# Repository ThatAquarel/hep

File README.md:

# [Dawson HEP](https://youtu.be/Yp-H1ZBjPuM)

Introduction Video:

## About us

**The Dawson High Energy Physics** club, run by Dr. Manuel Toharia Zapata is a place for curious college students to learn more about particle physics. Every week, students from a wide variety of programs meet to learn and discuss about flavour physisc, extra dimensions and much more. We engage with both theory and experiments, learning about and observing particles. Our many projects include an Alpha particle detector, spark chamber, Scintillating Chamber, and more.

Here's a [video](https://youtu.be/Yp-H1ZBjPuM) about our group!

### [Alpha particle detector](./alpha_particle/README.md)

A solid-state alpha particle detector based off of [CERN'S DIY Alpha Particle Detector](https://github.com/ozel/DIY_particle_detector) design.

### [Higgs data analysis](./higgs_data_analysis/README.md)

Analyzing data from a Monte Carlo simulation to determine the mass of a hidden particle. This program is capable of finding a deviation from the noise and identify the mass of the unexpected particle.

### [Scintillating Chamber](./scintillator_field/README.md)

Our proposal to the 2025 [Beamline for schools](https://beamlineforschools.cern/) competition. It consists of an arrangement of scitillator rods to detect and model the trajectory of cosmic ray in three dimensions. The possible trajectories are then calculated and displayed graphically to the user.

**See Paper [HERE](./scintillator_field/proposal/proposal.pdf)**

## Contacts

- Milo Belarbi
- David Birnbaum
- Tykhon Byshkin
- Matvey Chirchikov
- Danah Dézémé
- Arij Mohamedi
- [Evan Parasol](https://github.com/TheBookwyrms), blackdragon6493@gmail.com
- [Leandro Perez-Moran](https://github.com/LudioRex), pemle2007@gmail.com
- Ari Polterovich
- [Tian Yi, Xia](https://github.com/ThatAquarel), xtxiatianyi@gmail.com
- [Andy Yu](https://github.com/Anodymous1), andy.yu@dawsoncollege.qc.ca
- [Aljoscha Ziegler](https://github.com/Questionning), ziegleraljoscha@gmail.com

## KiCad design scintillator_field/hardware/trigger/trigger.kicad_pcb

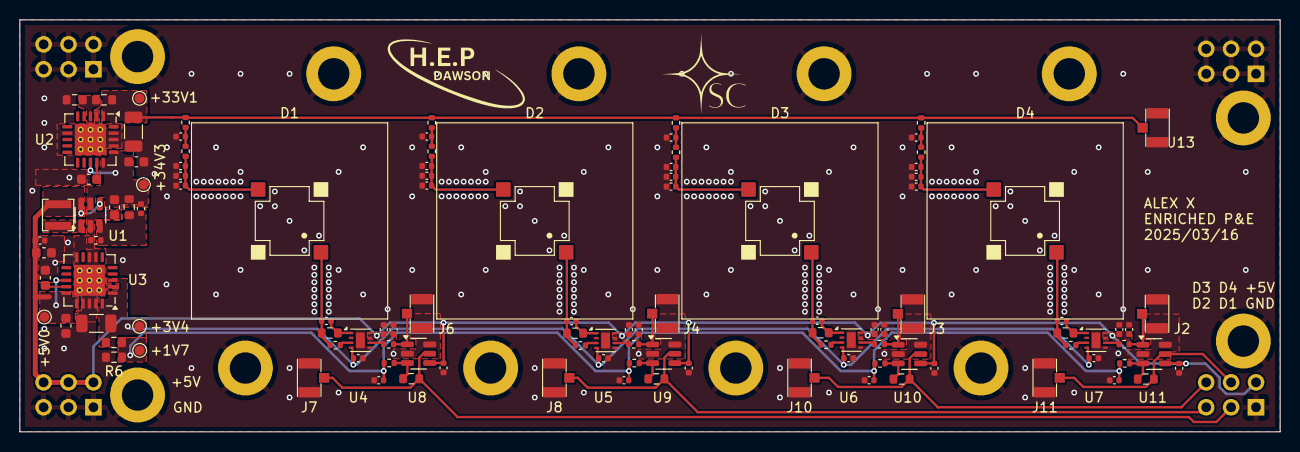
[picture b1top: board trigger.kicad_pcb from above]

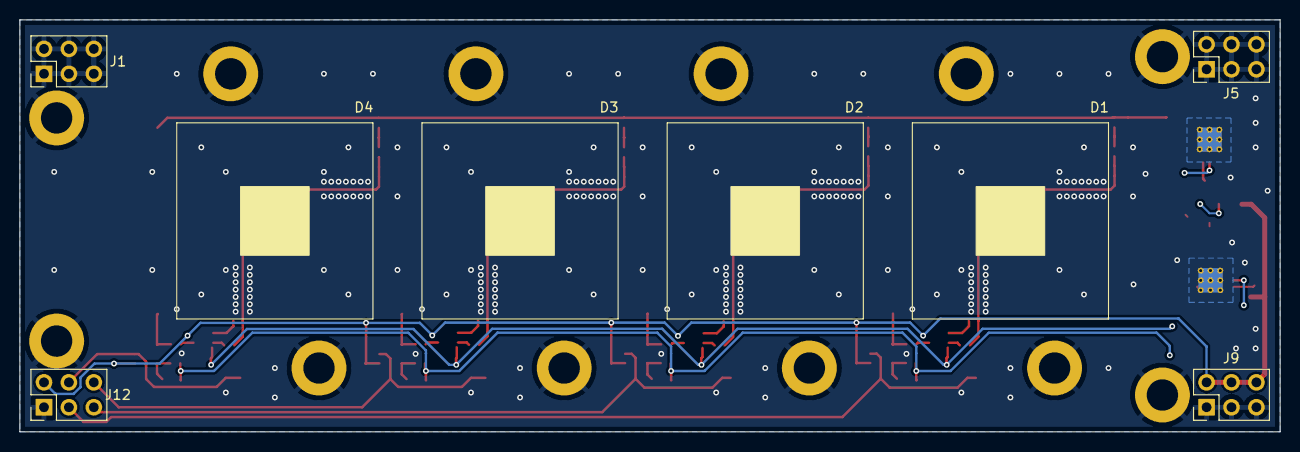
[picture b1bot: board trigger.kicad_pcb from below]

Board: 2 copper layers, 128.5 x 42.0 mm, 130 parts (4 on the bottom side), 47 nets.

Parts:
+1V7, +3V4, +5V0, +33V1, +34V3: TestPoint; TestPoint_Pad_D1.0mm
C1: 22p; C_0402_1005Metric
C2, C31, C32, C33, C34, C41, C42, C43, C44: 0.1u; C_0402_1005Metric
C3, C4, C5, C6, C8, C9: 1u; C_0603_1608Metric
C7, C10: 10u; C_1206_3216Metric
C11, C12, C13, C14, C15, C16, C17, C18, C19, C20, C21, C22, C23, C24, C25, C26, C37, C38, C39, C40, C47, C48, C49, C50: 10n; C_0402_1005Metric
C27, C28, C29, C30: 3p; C_0402_1005Metric
C35, C36, C45, C46: 2.2u; C_0402_1005Metric
D1, D2, D3, D4: MICROFC-60035-SMT-TR SIPM; MICROFC-60035-SMT-TR
H1, H2, H3, H4, H5, H6, H7, H8, H9, H10, H11, H12: M3; MountingHole_3.2mm_M3_DIN965_Pad
J1, J5, J9, J12: Conn_02x03_Top_Bottom; PinHeader_2x03_P2.54mm_Vertical
J2, J3, J4, J6, J7, J8, J10, J11, J13: Conn_Coaxial_Small; BWIPX-1-001E
L1: 22u; L_Murata_LQH3NPN_3.0x3.0mm
R1: 12k 0.1%; R_0402_1005Metric
R2: 316k 0.1%; R_0603_1608Metric
R3, R19, R20, R21, R22: 226k 0.1%; R_0603_1608Metric
R4, R5, R6, R31, R32, R33, R34: 10k 0.1%; R_0603_1608Metric
R7, R8, R9, R10, R11, R12, R13, R14, R27, R28, R29, R30: 49.9R; R_0402_1005Metric
R15, R16, R17, R18: 20R; R_0402_1005Metric
R23, R24, R25, R26: 0; R_0402_1005Metric
U1: LT3461A; TSOT-23-6
U2, U3: TPS7A4701; Texas_RGW0020A_VQFN-20-1EP_5x5mm_P0.65mm_EP3.15x3.15mm_Ther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
U4, U5, U6, U7: OPA858xDSG; WSON-8-1EP_2x2mm_P0.5mm_EP0.9x1.6mm
U8, U9, U10, U11: TLV3501AIDBV; SOT-23-6

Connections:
+1.7V: +1V7.1, C37.1, C38.1, C47.1, C48.1, R5.2, R6.1, R27.2, R28.2, R29.2, R30.2
+3.4V: +3V4.1, C10.1, C39.1, C40.1, C49.1, C50.1, R5.1, U3.1 (OUT), U3.3 (SENSE/FB), U3.20 (OUT), U4.4 (+), U5.4 (+), U6.4 (+), U7.4 (+)
+5V: +5V0.1, C2.1, C3.1, C8.1, C31.1, C32.1, C33.1, C34.1, C35.1, C36.1, C41.1, C42.1, C43.1, C44.1, C45.1, C46.1, J9.4, J9.5, J9.6, J12.4, L1.2, U1.4 (SHDN), U1.6 (VIN), U3.13 (EN), U3.15 (IN), U3.16 (IN), U4.7 (V+), U4.8 (~PD), U5.7 (V+), U5.8 (~PD), U6.7 (V+), U6.8 (~PD), U7.7 (V+), U7.8 (~PD), U8.4 (V+), U9.4 (V+), U10.4 (V+), U11.4 (V+)
+33.1V: +33V1.1, C7.1, J13.1 (In), R3.1, R7.1, R8.1, R9.1, R10.1, U2.1 (OUT), U2.20 (OUT)
+34.3V: +34V3.1, C1.2, C4.1, C5.1, R2.2, U1.5 (VOUT), U2.13 (EN), U2.15 (IN), U2.16 (IN)
/amplifiers/AOUT1: J6.1 (In), R23.2, U8.1 (-)
/amplifiers/AOUT2: J4.1 (In), R24.2, U9.1 (-)
/amplifiers/AOUT3: J3.1 (In), R25.2, U10.1 (-)
/amplifiers/AOUT4: J2.1 (In), R26.2, U11.1 (-)
/amplifiers/DOUT1: J7.1 (In), J12.2, R31.2, U8.5
/amplifiers/DOUT2: J8.1 (In), J12.3, R32.2, U9.5
/amplifiers/DOUT3: J10.1 (In), J12.6, R33.2, U10.5
/amplifiers/DOUT4: J11.1 (In), J12.5, R34.2, U11.5
/amplifiers/IN1: C27.1, D1.2 (A), R15.1, R19.1
/amplifiers/IN2: C28.1, D2.2 (A), R16.1, R20.1
/amplifiers/IN3: C29.1, D3.2 (A), R17.1, R21.1
/amplifiers/IN4: C30.1, D4.2 (A), R18.1, R22.1
GND: C2.2, C3.2, C4.2, C5.2, C6.2, C7.2, C8.2, C9.2, C10.2, C11.2, C12.2, C13.2, C14.2, C15.2, C16.2, C17.2, C18.2, C19.2, C20.2, C21.2, C22.2, C23.2, C24.2, C25.2, C26.2, C31.2, C32.2, C33.2, C34.2, C35.2, C36.2, C37.2, C38.2, C39.2, C40.2, C41.2, C42.2, C43.2, C44.2, C45.2, C46.2, C47.2, C48.2, C49.2, C50.2, H1.1, H2.1, H3.1, H4.1, H5.1, H6.1, H7.1, H8.1, H9.1, H10.1, H11.1, H12.1, J1.1, J1.2, J1.3, J1.4, J1.5, J1.6, J2.2 (Ext), J3.2 (Ext), J4.2 (Ext), J5.1, J5.2, J5.3, J5.4, J5.5, J5.6, J6.2 (Ext), J7.2 (Ext), J8.2 (Ext), J9.1, J9.2, J9.3, J10.2 (Ext), J11.2 (Ext), J12.1, J13.2 (Ext), R1.1, R4.2, R6.2, U1.2 (GND), U2.2 (NC), U2.7 (GND), U2.17 (NC), U2.18 (NC), U2.19 (NC), U2.21 (EP), U3.2 (NC), U3.7 (GND), U3.8 (1.6V), U3.10 (0.4V), U3.17 (NC), U3.18 (NC), U3.19 (NC), U3.21 (EP), U4.5 (V-), U4.9 (V-), U5.5 (V-), U5.9 (V-), U6.5 (V-), U6.9 (V-), U7.5 (V-), U7.9 (V-), U8.2 (V-), U8.6 (SHDN), U9.2 (V-), U9.6 (SHDN), U10.2 (V-), U10.6 (SHDN), U11.2 (V-), U11.6 (SHDN)
unnamed: C11.1, R7.2, R11.1
unnamed: C12.1, R8.2, R12.1
unnamed: C13.1, R9.2, R13.1
unnamed: C14.1, R10.2, R14.1
unnamed: C15.1, C19.1, C23.1, D1.1 (K), R11.2
unnamed: C16.1, C20.1, C24.1, D2.1 (K), R12.2
unnamed: C17.1, C21.1, C25.1, D3.1 (K), R13.2
unnamed: C18.1, C22.1, C26.1, D4.1 (K), R14.2
unnamed: R23.1, U4.6
unnamed: R24.1, U5.6
unnamed: R25.1, U6.6
unnamed: R26.1, U7.6
unnamed: C1.1, R1.2, R2.1, U1.3 (FB)
unnamed: L1.1, U1.1 (SW)
unnamed: C6.1, U2.14 (NR)
unnamed: R3.2, R4.1, U2.3 (SENSE/FB)
unnamed: C9.1, U3.14 (NR)
unnamed: R15.2, U4.3 (-)
unnamed: C27.2, R19.2, U4.1 (FB)
unnamed: R16.2, U5.3 (-)
unnamed: C28.2, R20.2, U5.1 (FB)
unnamed: R17.2, U6.3 (-)
unnamed: C29.2, R21.2, U6.1 (FB)
unnamed: R18.2, U7.3 (-)
unnamed: C30.2, R22.2, U7.1 (FB)
unnamed: R27.1, R31.1, U8.3 (+)
unnamed: R28.1, R32.1, U9.3 (+)
unnamed: R29.1, R33.1, U10.3 (+)
unnamed: R30.1, R34.1, U11.3 (+)

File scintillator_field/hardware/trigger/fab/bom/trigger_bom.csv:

Comment,Designator,Footprint,LCSC
"22p, 50V",C1,Capacitor_SMD:C_0402_1005Metric,C70464
"10n, 50V","C11,C12,C13,C14,C15,C16,C17,C18,C19,C20,C21,C22,C23,C24,C25,C26,C37,C38,C39,C40,C47,C48,C49,C50",Capacitor_SMD:C_0402_1005Metric,C1524
"0.1u, 50V","C2,C31,C32,C33,C34,C41,C42,C43,C44",Capacitor_SMD:C_0402_1005Metric,C1581
"3p, 50V","C27,C28,C29,C30",Capacitor_SMD:C_0402_1005Metric,C1564
"1u, 50V","C3,C4,C5,C6,C8,C9",Capacitor_SMD:C_0603_1608Metric,C15849
"2.2u, 10V","C35,C36,C45,C46",Capacitor_SMD:C_0402_1005Metric,C60078
"10u, 50V","C7,C10",Capacitor_SMD:C_1206_3216Metric,C13585
"Conn_Coaxial_Small, I-PEX MHF1","J2,J3,J4,J6,J7,J8,J10,J11,J13",connectors:BWIPX-1-001E,C496552
22uH,L1,lqh3npn:L_Murata_LQH3NPN_3.0x3.0mm,C237408
12k 0.1%,R1,Resistor_SMD:R_0402_1005Metric,C317927
20R,"R15,R16,R17,R18",Resistor_SMD:R_0402_1005Metric,C25089
316k 0.1%,R2,Resistor_SMD:R_0603_1608Metric,C861317
0R,"R23,R24,R25,R26",Resistor_SMD:R_0402_1005Metric,C17168
226k 0.1%,"R3,R19,R20,R21,R22",Resistor_SMD:R_0603_1608Metric,C861233
10k 0.1%,"R4,R5,R6,R31,R32,R33,R34",Resistor_SMD:R_0603_1608Metric,C136139
49.9R,"R7,R8,R9,R10,R11,R12,R13,R14,R27,R28,R29,R30",Resistor_SMD:R_0402_1005Metric,C25120
LT3461A,U1,Package_TO_SOT_SMD:TSOT-23-6,C481768
TPS7A4701,"U2,U3",Package_DFN_QFN:Texas_RGW0020A_VQFN-20-1EP_5x5mm_P0.65mm_EP3.15x3.15mm_ThermalVias,C90084
OPA858xDSG,"U4,U5,U6,U7",Package_SON:WSON-8-1EP_2x2mm_P0.5mm_EP0.9x1.6mm,C970232
TLV3501AIDBV,"U8,U9,U10,U11",Package_TO_SOT_SMD:SOT-23-6,C193413

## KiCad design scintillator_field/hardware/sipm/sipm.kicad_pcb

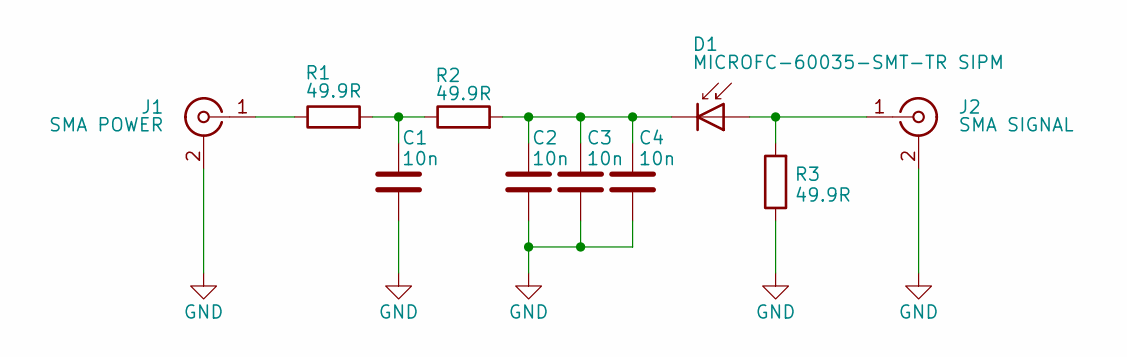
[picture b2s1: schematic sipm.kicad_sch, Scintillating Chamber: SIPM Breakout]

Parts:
C1, C2, C3, C4: 10n; C_0805_2012Metric_Pad1.18x1.45mm_HandSolder
D1: MICROFC-60035-SMT-TR SIPM; MICROFC-60035-SMT-TR
J1: SMA POWER; SMA_Amphenol_901-144_Vertical
J2: SMA SIGNAL; SMA_Amphenol_901-144_Vertical
R1, R2, R3: 49.9R; R_0805_2012Metric_Pad1.20x1.40mm_HandSolder

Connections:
GND: C1.2, C2.2, C3.2, C4.2, J1.2 (Ext), J2.2 (Ext), R3.1
unnamed: C1.1, R1.2, R2.1
unnamed: D1.2 (A), J2.1 (In), R3.2
unnamed: C2.1, C3.1, C4.1, D1.1 (K), R2.2
unnamed: J1.1 (In), R1.1

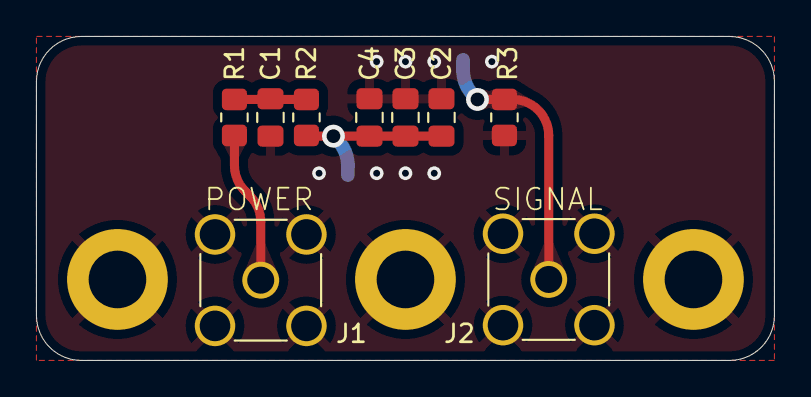
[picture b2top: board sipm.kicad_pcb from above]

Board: 2 copper layers, 41.0 x 18.0 mm, 10 parts (1 on the bottom side), 5 nets.

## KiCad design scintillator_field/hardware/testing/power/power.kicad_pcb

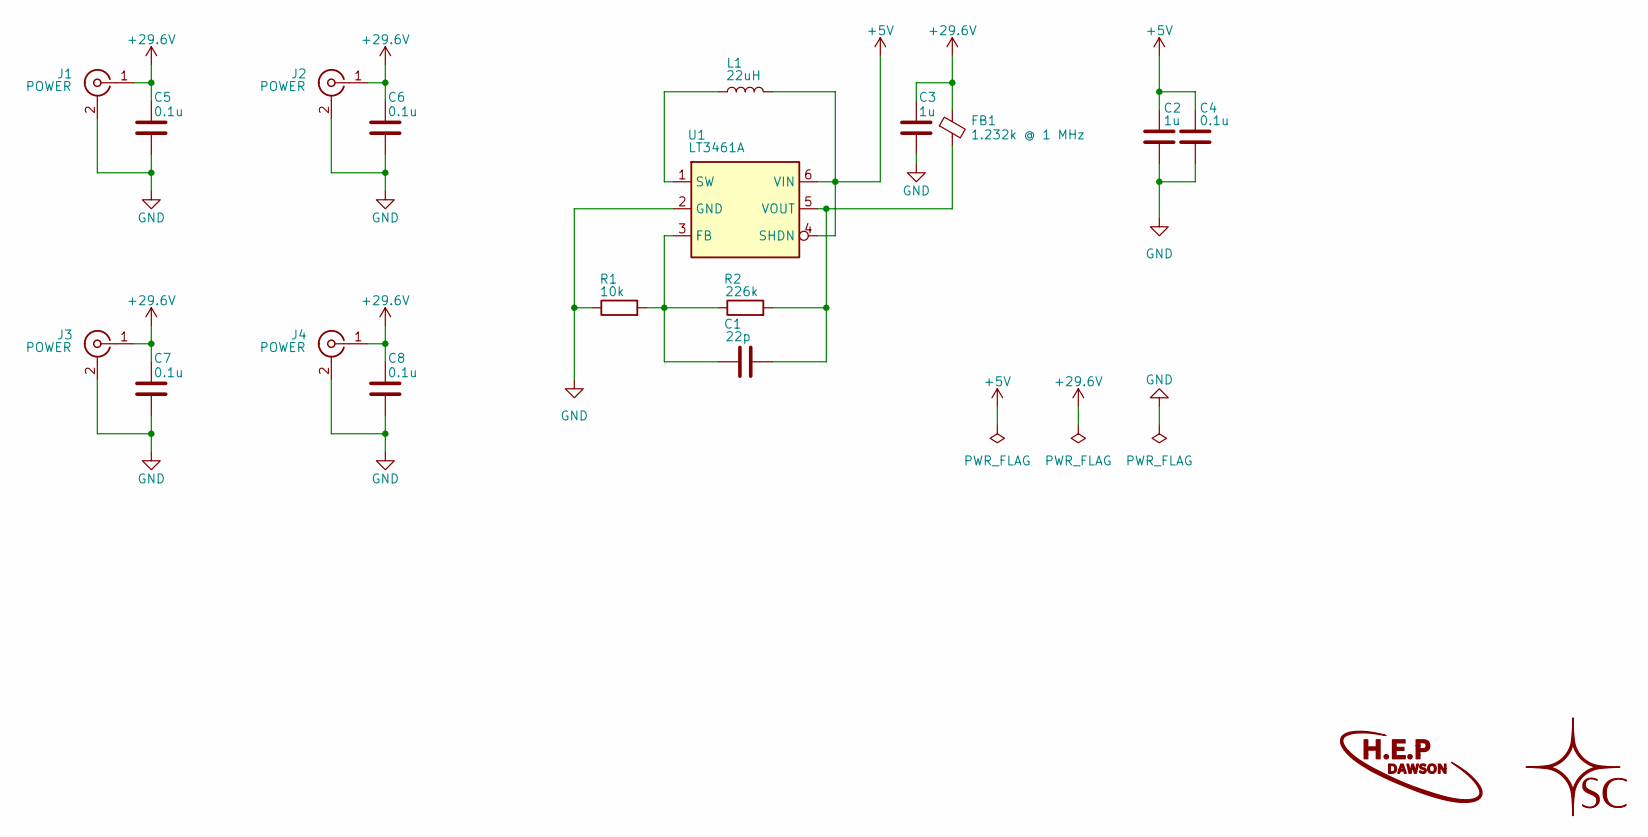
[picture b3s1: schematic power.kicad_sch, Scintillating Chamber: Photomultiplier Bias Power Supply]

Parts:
C1: 22p; C_0805_2012Metric_Pad1.18x1.45mm_HandSolder
C2, C3: 1u; C_0805_2012Metric_Pad1.18x1.45mm_HandSolder
C4, C5, C6, C7, C8: 0.1u; C_0805_2012Metric_Pad1.18x1.45mm_HandSolder
FB1: 1.232k @ 1 MHz; FB_TDK_VFS6045_2424_6060Metric_HandSoldering
J1, J2, J3, J4: POWER; SMA_Amphenol_901-144_Vertical
L1: 22uH; L_Laird_TYS3015_HandSoldering
R1: 10k; R_0805_2012Metric_Pad1.20x1.40mm_HandSolder
R2: 226k; R_0805_2012Metric_Pad1.20x1.40mm_HandSolder
U1: LT3461A; TSOT-23-6_HandSoldering

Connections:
+5V: C2.1, C4.1, L1.2, U1.4 (SHDN), U1.6 (VIN)
+29.6V: C3.1, C5.1, C6.1, C7.1, C8.1, FB1.1, J1.1 (In), J2.1 (In), J3.1 (In), J4.1 (In)
GND: C2.2, C3.2, C4.2, C5.2, C6.2, C7.2, C8.2, J1.2 (Ext), J2.2 (Ext), J3.2 (Ext), J4.2 (Ext), R1.1, U1.2 (GND)
unnamed: C1.1, R1.2, R2.1, U1.3 (FB)
unnamed: L1.1, U1.1 (SW)
unnamed: C1.2, FB1.2, R2.2, U1.5 (VOUT)

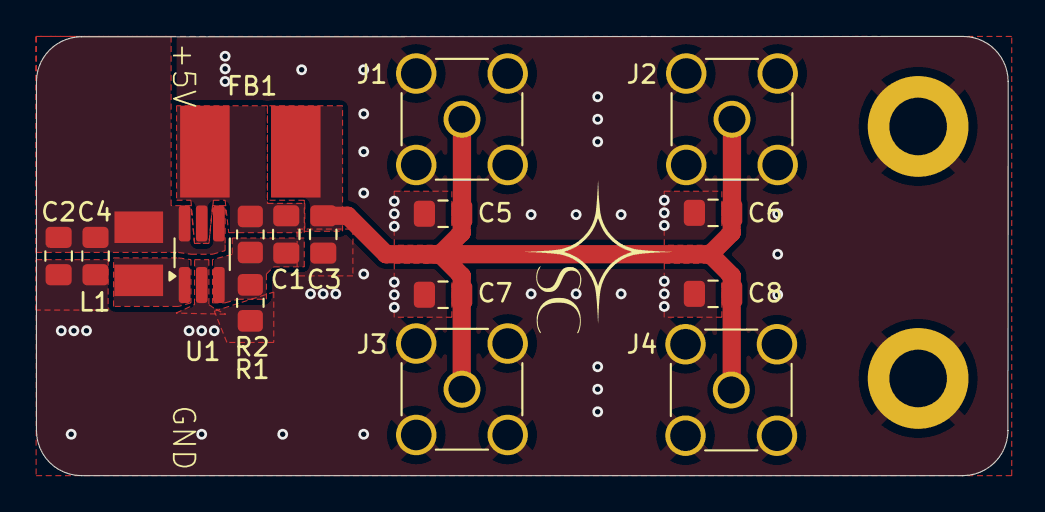
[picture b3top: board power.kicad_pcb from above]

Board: 2 copper layers, 54.0 x 24.4 mm, 17 parts (0 on the bottom side), 6 nets.

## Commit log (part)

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2025-03-17 3D structure rods configuration, x and y axes
2025-03-17 finalize pcb
2025-03-18 clean up display code, add some documentation
2025-03-18 pcb fabrication files
2025-03-18 shaders tests
2025-03-18 shaders mac
2025-03-19 acquisition pcb
2025-03-20 fix trigger pcb
2025-03-20 update to opa858
2025-03-20 fabrication for trigger
2025-03-20 First version of boundary creation algorithm
2025-03-23 usb-c
2025-03-23 fpga pll latching detection
2025-03-24 Implemented input for both side views
2025-03-24 Implemented input for 2 side views
2025-03-26 expensese
2025-03-26 invoice
2025-03-26 receipts
2025-03-26 Create bl4s_proposal.tex
    LaTeX file containing the Scintilating Chamber BL4S proposal. Updated regularly from Proposal.doc on the Google Drive repository: https://drive.google.com/drive/folders/19_MMcoH1Qw7MvBGZwiW7HJuY0r8M6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
2025-03-27 top and bottom sections of detector
2025-03-27 finances
2025-03-27 Added another visualizer(work in progress)
2025-03-28 Now returns hull bounds (y is assumed to be extended)
2025-03-28 visualizer in display_2, if this works
2025-03-28 Famework and rename bl4s_proposal.tex to main.tex
    Added some of the framework for the main file.
2025-03-28 Create README.md (bare bones)
2025-03-28 display_1 uses shaders
2025-03-28 removed opengl matrix viewing and projection functions
2025-03-28 Version that will have bugs
2025-03-28 Removed bugs
2025-03-28 Minor clean up
2025-03-28 show convex hull for arbitraty test points
2025-03-28 integrated Aljoscha's code
2025-03-29 Added code for fans
2025-03-29 Input all section files
2025-03-30 Added binary-to-list function
2025-04-04 Fixed bugs caused by (1, 1) type inputs
2025-04-04 added description.txt
2025-04-05 converted scintillator field to module scintillator_field. hull detection display with points works properly (test data in get_hull_returns), hull detection using detection.py has errors.
2025-04-06 Update acknowledgements.tex
    Full version of the acknowledgements
2025-04-06 Update introduction.tex
    Full version of the introduction. NOT FINAL, subject to change.
2025-04-06 Create community_outreach
2025-04-06 almost ready to go(only have to fix coordinates)
2025-04-06 Fixed the rods lighting up on click feature
2025-04-06 pins of registers
2025-04-06 arduino code
2025-04-06 fpga signal shift register
2025-04-06 serial communication
2025-04-06 new pins
2025-04-07 Test fix
2025-04-07 Fixed reference system
2025-04-07 Cleaner version
2025-04-07 Right values now
2025-04-07 to save
2025-04-08 fixed units
2025-04-08 Converted to class, thanks to Evan!
2025-04-08 Fixed value resetting
2025-04-08 display_1 shows proper display, uses correct size
2025-04-08 fpga all working
2025-04-08 cleanup repo tree
2025-04-08 now works
2025-04-08 serial reading
2025-04-08 arduino input for display_1
2025-04-08 hull_bounds error
2025-04-08 crash error fix attempt
2025-04-09 display and detector work, error patched
2025-04-09 xyz axis
2025-04-09 Changed test.py into a class(data_manager)
2025-04-09 clicking detection now works
2025-04-09 fixed lighting up and added (1,1) compatibility
2025-04-09 works
2025-04-09 fixed typo
2025-04-09 serial testing
2025-04-09 lights up by default
2025-04-09 work
2025-04-09 signal to noise ratio adjustement
2025-04-09 data input & camera clipping
2025-04-09 refactor verilog
2025-04-09 displays time, generate csv
2025-04-10 fixed turning off lighting(also just to save)
2025-04-10 refactor hardware
2025-04-10 refactor acquisition
2025-04-10 display_1 works for real data. data from 2025-04-09 run.
2025-04-10 Fixed lighting up; test.data now has 1 less layer
2025-04-10 latex gitignores
2025-04-10 latex proposal
2025-04-10 Applied binary conversion
2025-04-12 dual display test
2025-04-12 basic refactor for dual viewport
2025-04-12 remove old boundary package
2025-04-12 refactor module
2025-04-12 add convex tests
2025-04-12 testing gitignore
2025-04-12 cleanup tree
2025-04-12 copy impl_b
2025-04-12 basic viewporting impl_a
2025-04-12 dual viewports for impl_a
2025-04-12 add data manager tests
2025-04-12 refactor imports
2025-04-12 dual viewport wrappers
2025-04-12 viewports focus manipulation
2025-04-12 remove impl_b manual entrypoint
2025-04-12 callback none protection
2025-04-12 viewport rendering ratios
2025-04-12 fixed side controls
2025-04-12 load fonts
2025-04-12 add logo + text
2025-04-12 dual viewports testing
2025-04-14 long-term data acquisition
2025-04-16 fix time and location of csv saving windows
2025-04-16 impl a and b data manager and arduino in single file, compatible for both
2025-04-16 data recorder failure add
2025-04-16 long term
2025-04-16 long term print
2025-04-16 set logging level
2025-04-16 first round data
2025-04-17 excel .gitignore
2025-04-17 transfer receipts
2025-04-17 removed fan_out from Evan and Andy's code, still remains in Aljoscha's code. only generates data csv if not debugging (having actual data)
2025-04-17 small refactoring, including minor compatibility fixes
2025-04-17 new data
2025-04-17 long term data analysis
2025-04-17 data collection
2025-04-18 add receipts
2025-04-18 badly working imgui checkboxes impl_b
2025-04-18 funding
2025-04-18 intersection test
2025-04-18 long term analysis reindex + reliability
2025-04-19 partially working double checkboxes in impl_controls
2025-04-19 data display with checkboxes
2025-04-19 unified imgui
2025-04-19 data apr-19
2025-04-20 universal camera, shaders for both
2025-04-20 impl_b colour changes for point, some inconsistency in results between test data points
2025-04-20 small refactor
2025-04-20 pyserial singleton class, non-debug should work, condensed entrypoint
2025-04-20 moved universal values to compat
2025-04-21 add proposal
2025-04-21 new hardware
2025-04-21 remove data
2025-04-22 data .gitignore
2025-04-22 add up5k update
2025-04-22 reg latch testing
2025-04-23 acquisition v2 basics
2025-04-23 24 mhz oscillator
2025-04-27 marginally improved light up and structure for impl b
2025-05-04 refactor imgui into tables
2025-05-04 demo works
2025-05-05 demo at start
2025-05-06 fixed demo crash bug, added pause button and escape key
2025-05-06 added button for pause
2025-05-07 fixed 1.57 million vao creation effect, added DataPoint class, fixed data column length issue between demo and debug
2025-05-09 last commit before merge
2025-05-12 Initial function setup Added data parsing, copied from data_compilation_all.py. Detailed rough class structure.
2025-06-23 .gitignore
2025-06-23 fix inv mass calculation
2025-06-23 update test
2025-06-23 graph
2025-06-23 ignore csv
2025-06-23 graphs
2025-06-23 optimize
2025-06-23 histogram
2025-06-23 optimize inv mass
2025-06-23 comment
2025-06-23 scintillators
2025-06-23 move
2025-06-23 alpha particle detector
2025-06-23 remove
2025-06-23 comments
2025-06-23 SiPM breakout board
2025-06-23 scintillator funding
2025-06-23 hardware images
2025-06-23 logo sizes
2025-06-23 first precision simulation
2025-06-23 logos
2025-06-23 finalized SiPM PCB
2025-06-23 field optimization
2025-06-23 scintillator hardware
2025-06-23 arduino testing
2025-06-23 run drc
2025-06-23 fix ground planes
2025-06-23 fix display folder name
2025-06-23 and gate
2025-06-23 trigger pcb rework
2025-06-23 conclude schematic
2025-06-23 expenses
2025-06-23 fpga basic flash programming
2025-06-23 extra commands
2025-06-23 power PCB
2025-06-23 pcb v1
2025-06-23 refactor power
2025-06-23 sipm PCB updates
2025-06-23 empty window for display
2025-06-23 trigger pcb
2025-06-23 power
2025-06-23 update images
2025-06-23 First parts of the aquisition pcb design
2025-06-23 update video link
2025-06-23 Small changes on all sheets
2025-06-23 demo gif
